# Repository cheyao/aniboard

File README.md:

# Aniboard - Anime themed keyboard

*Insert Final Product Picture*

Made by cyao: `@Cyao` on slack, github.com/cheyao

Features:
- 88x keys!
- Morally correct Alt, Command, Control layout
- 0.91" OLED for your favourite pictures
- 88x Neopixels capable of eating 5.28A! Portable hand warmer :3
- Optional triple USB power input to feed all the hungry neopixels.
- Cute anime silkscreens! (Open PCB in KiCAD and zoom out to find a easter egg :3)
- Adaptive power MUXing and overcurrent fail safes
- Multiple fail safes, optional solder bridge configs
- Super compact design
- Self define tilt (Go edit in `CAD/constants.scad` and regenerate)
- Employes metal electrode leadless face technology to ensure high-reliability and precision with predictable characteristics
- High accuracy, long-term stability, moisture resistance, high-temperature resistance
- Made with precise Hot Air solder reflow technology
- KMK firmware, live edit your keymaps

## PCB 

The PCB's size is 355x120mm

| Schematic |
| - |
|  |

| Two sides |
| - |
|  |

| Front |
| - |
|  |

| Back |
| - |
|  |

3D render pictures:

## Case

The case v1 is fully parametric and made with OpenSCAD, allowed me to make a online case generator. Link after the YSWS ends.

V2 is made with freecad, and is of top mount style.

I chose to not add any engraving since it will look bad. I would want to print my case In school with ams and custom colored fillament when I buy some new fillament. (I need hq to print my case in white for the moment)

## BOM

These were old prices for aliexpress, see bottom for lcsc prices (better)

| Name                             | Qty | Price (EUR) |
| -------------------------------- | --- | ----------- |
| 0.91" OLED SSD1306               | 1   | |
| 0.1uf 0805 capacitors            | 90  | |
| 4.7uf 0805 capacitors            | 3   | |
| 1uf   0805 capacitor             | 3   | |
| MiniMELF diodes                  | 88  | |
| 0603 GLED Vf2.1 30mA             | 7   | |
| USB-C Receptacles                | 2   | |
| SK6812MINI-E                     | 88  | |
| 470Ω 0805 resistor               | 5   | |
| 4.7kΩ 0805 resistor              | 5   | |
| 5.1kΩ 0805 resistor              | 4   | |
| 10kΩ 0805 resistor               | 2   | |
| 1kΩ 0805 resistor                | 2   | |
| 200Ω 0805 resistor               | 3   | |
| TPS2116DRL                       | 2   | |
| SN74LVC1T45DBVR                  | 1   | |
| CH224K                           | 2   | |
| ESP12-E                          | 1   | |
| Orph/Raspberry Pi Pico           | 1   | High Seas   |
| Case (Preferably pink, else white "./production/case.3mf") | 1 | Me |
| Acrylic ("./production/acrylic.dxf") | 1 | Hack Club |
| M2 Heatset Inserts 4OD 4mm       | 28  | 1.74        |
| M2 Torx Thin Head Bolts 5mm 14mm | 16  | 2.08        |
| M2 Torx Thin Head Bolts 5mm 5mm  | 12  | 1.62        |
| JWK Cupid Switch                 | 88  | 36.60/w ship|
| 2u MX stabilizor                 | 5   | 27.99 (20$ new member) |
| 6.25u MX stabilizer              | 1   | ^           |

Old:

| Total Price | PCB      | Switches | Fasteners | Keycaps  | Stabilizers | Other     |
| ----------- | -------- | -------- | --------- | -------- | ----------- | --------- |
| 120.63/ws   | 37.00/ws | 38.81/ws | 5.44/ns   | 21.79/ws | 19.59/ns    | ~24.03/ws |

2$ More in PCB for lead free HASL!

Please add this grant to my High Seas Digikey grant! <3

~The stabs are 22.38 USD so going to transfer 5$ to HQ.~ Done, https://hcb.hackclub.com/hackpad/donations - Chengyin Yao aka Cyao

~Uhh I think the TX are still over budget? Gonna figure something out.~ Found in budget TX! Gonna abuse new member discount lol.

The LCSC cart might seem to have excess of some components, it's either: minimal quanitity, or at the end I could spend 2.7$ more to save 6$ so why not

Cupid: https://keygem.com/products/cupid-switch-group-buy-10pcs?variant=44806087770380

## Notes:

This got me 60h on cafe :sob:

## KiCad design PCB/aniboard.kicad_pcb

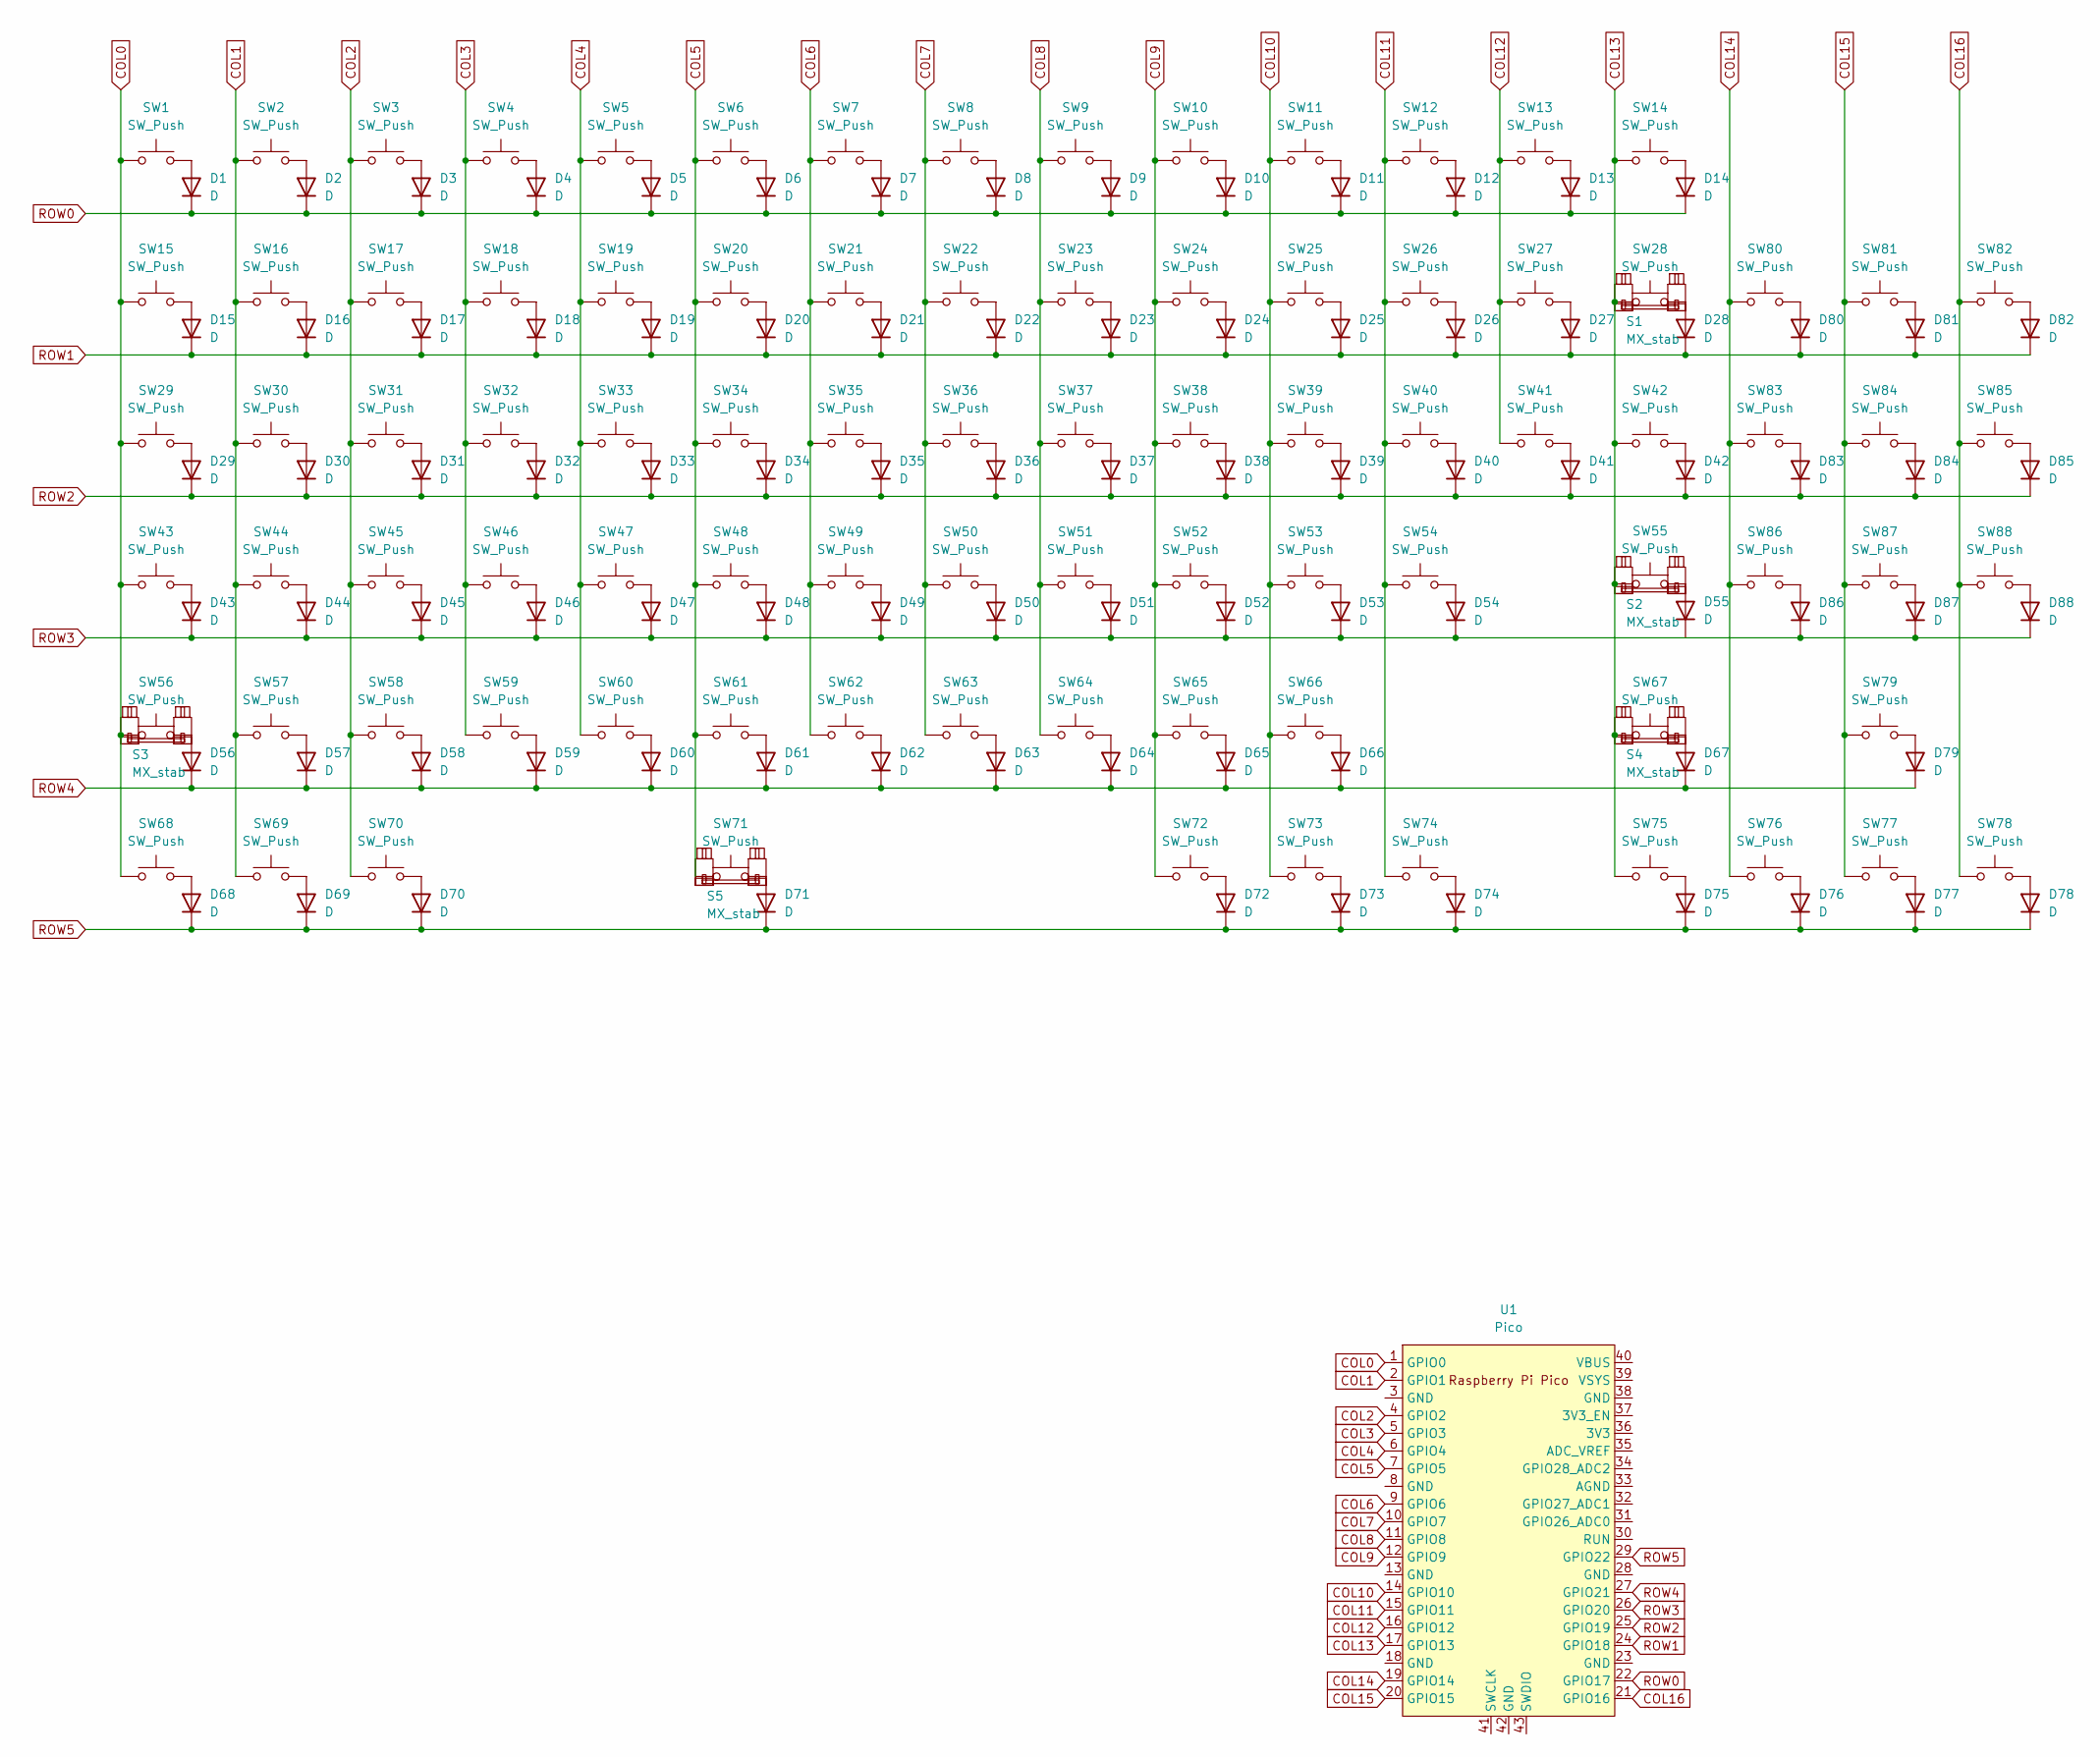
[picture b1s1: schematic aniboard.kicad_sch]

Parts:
D1, D2, D3, D4, D5, D6, D7, D8, D9, D10, D11, D12, D13, D14, D15, D16, D17, D18, D19, D20, D21, D22, D23, D24, D25, D26, D27, D28, D29, D30, D31, D32, D33, D34, D35, D36, D37, D38, D39, D40, D41, D42, D43, D44, D45, D46, D47, D48, D49, D50, D51, D52, D53, D54, D55, D56, D57, D58, D59, D60, D61, D62, D63, D64, D65, D66, D67, D68, D69, D70, D71, D72, D73, D74, D75, D76, D77, D78, D79, D80, D81, D82, D83, D84, D85, D86, D87, D88: D; D_DO-35_SOD27_P7.62mm_Horizontal
S1: MX_stab; STAB_MX_2u
S2, S3: MX_stab; STAB_MX_2.25u
S4: MX_stab; STAB_MX_2.75u
S5: MX_stab; STAB_MX_6.25u
SW1, SW14, SW29, SW42: SW_Push; SW_MX_1.5u
SW2, SW3, SW4, SW5, SW6, SW7, SW8, SW9, SW10, SW11, SW12, SW13, SW15, SW16, SW17, SW18, SW19, SW20, SW21, SW22, SW23, SW24, SW25, SW26, SW27, SW28, SW30, SW31, SW32, SW33, SW34, SW35, SW36, SW37, SW38, SW39, SW40, SW41, SW44, SW45, SW46, SW47, SW48, SW49, SW50, SW51, SW52, SW53, SW54, SW55, SW56, SW57, SW58, SW59, SW60, SW61, SW62, SW63, SW64, SW65, SW66, SW67, SW71, SW76, SW77, SW78, SW79, SW80, SW81, SW82, SW83, SW84, SW85, SW86, SW87, SW88: SW_Push; SW_MX_1u
SW43: SW_Push; SW_MX_1.75u
SW68, SW69, SW70, SW72, SW73, SW74, SW75: SW_Push; SW_MX_1.25u
U1: Pico; RPi_Pico_SMD_TH

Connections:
COL0: SW1.1, SW15.1, SW29.1, SW43.1, SW56.1, SW68.1, U1.1 (GPIO0)
COL1: SW2.1, SW16.1, SW30.1, SW44.1, SW57.1, SW69.1, U1.2 (GPIO1)
COL2: SW3.1, SW17.1, SW31.1, SW45.1, SW58.1, SW70.1, U1.4 (GPIO2)
COL3: SW4.1, SW18.1, SW32.1, SW46.1, SW59.1, U1.5 (GPIO3)
COL4: SW5.1, SW19.1, SW33.1, SW47.1, SW60.1, U1.6 (GPIO4)
COL5: SW6.1, SW20.1, SW34.1, SW48.1, SW61.1, SW71.1, U1.7 (GPIO5)
COL6: SW7.1, SW21.1, SW35.1, SW49.1, SW62.1, U1.9 (GPIO6)
COL7: SW8.1, SW22.1, SW36.1, SW50.1, SW63.1, U1.10 (GPIO7)
COL8: SW9.1, SW23.1, SW37.1, SW51.1, SW64.1, U1.11 (GPIO8)
COL9: SW10.1, SW24.1, SW38.1, SW52.1, SW65.1, SW72.1, U1.12 (GPIO9)
COL10: SW11.1, SW25.1, SW39.1, SW53.1, SW66.1, SW73.1, U1.14 (GPIO10)
COL11: SW12.1, SW26.1, SW40.1, SW54.1, SW74.1, U1.15 (GPIO11)
COL12: SW13.1, SW27.1, SW41.1, U1.16 (GPIO12)
COL13: SW14.1, SW28.1, SW42.1, SW55.1, SW67.1, SW75.1, U1.17 (GPIO13)
COL14: SW76.1, SW80.1, SW83.1, SW86.1, U1.19 (GPIO14)
COL15: SW77.1, SW79.1, SW81.1, SW84.1, SW87.1, U1.20 (GPIO15)
COL16: SW78.1, SW82.1, SW85.1, SW88.1, U1.21 (GPIO16)
unnamed: D1.2 (A), SW1.2
unnamed: D2.2 (A), SW2.2
unnamed: D3.2 (A), SW3.2
unnamed: D4.2 (A), SW4.2
unnamed: D5.2 (A), SW5.2
unnamed: D6.2 (A), SW6.2
unnamed: D7.2 (A), SW7.2
unnamed: D8.2 (A), SW8.2
unnamed: D9.2 (A), SW9.2
unnamed: D10.2 (A), SW10.2
unnamed: D11.2 (A), SW11.2
unnamed: D12.2 (A), SW12.2
unnamed: D13.2 (A), SW13.2
unnamed: D14.2 (A), SW14.2
unnamed: D15.2 (A), SW15.2
unnamed: D16.2 (A), SW16.2
unnamed: D17.2 (A), SW17.2
unnamed: D18.2 (A), SW18.2
unnamed: D19.2 (A), SW19.2
unnamed: D20.2 (A), SW20.2
unnamed: D21.2 (A), SW21.2
unnamed: D22.2 (A), SW22.2
unnamed: D23.2 (A), SW23.2
unnamed: D24.2 (A), SW24.2
unnamed: D25.2 (A), SW25.2
unnamed: D26.2 (A), SW26.2
unnamed: D27.2 (A), SW27.2
unnamed: D28.2 (A), SW28.2
unnamed: D29.2 (A), SW29.2
unnamed: D30.2 (A), SW30.2
unnamed: D31.2 (A), SW31.2
unnamed: D32.2 (A), SW32.2
unnamed: D33.2 (A), SW33.2
unnamed: D34.2 (A), SW34.2
unnamed: D35.2 (A), SW35.2
unnamed: D36.2 (A), SW36.2
unnamed: D37.2 (A), SW37.2
unnamed: D38.2 (A), SW38.2
unnamed: D39.2 (A), SW39.2
unnamed: D40.2 (A), SW40.2
unnamed: D41.2 (A), SW41.2
unnamed: D42.2 (A), SW42.2
unnamed: D43.2 (A), SW43.2
unnamed: D44.2 (A), SW44.2
unnamed: D45.2 (A), SW45.2
unnamed: D46.2 (A), SW46.2
unnamed: D47.2 (A), SW47.2
unnamed: D48.2 (A), SW48.2
unnamed: D49.2 (A), SW49.2
unnamed: D50.2 (A), SW50.2
unnamed: D51.2 (A), SW51.2
unnamed: D52.2 (A), SW52.2
unnamed: D53.2 (A), SW53.2
unnamed: D54.2 (A), SW54.2
unnamed: D55.2 (A), SW55.2
unnamed: D56.2 (A), SW56.2
unnamed: D57.2 (A), SW57.2
unnamed: D58.2 (A), SW58.2
unnamed: D59.2 (A), SW59.2
unnamed: D60.2 (A), SW60.2
unnamed: D61.2 (A), SW61.2
unnamed: D62.2 (A), SW62.2
unnamed: D63.2 (A), SW63.2
unnamed: D64.2 (A), SW64.2
unnamed: D65.2 (A), SW65.2
unnamed: D66.2 (A), SW66.2
unnamed: D67.2 (A), SW67.2
unnamed: D68.2 (A), SW68.2
unnamed: D69.2 (A), SW69.2
unnamed: D70.2 (A), SW70.2
unnamed: D71.2 (A), SW71.2
unnamed: D72.2 (A), SW72.2
unnamed: D73.2 (A), SW73.2
unnamed: D74.2 (A), SW74.2
unnamed: D75.2 (A), SW75.2
unnamed: D76.2 (A), SW76.2
unnamed: D77.2 (A), SW77.2
unnamed: D78.2 (A), SW78.2
unnamed: D79.2 (A), SW79.2
unnamed: D80.2 (A), SW80.2
unnamed: D81.2 (A), SW81.2
unnamed: D82.2 (A), SW82.2
unnamed: D83.2 (A), SW83.2
unnamed: D84.2 (A), SW84.2
unnamed: D85.2 (A), SW85.2
unnamed: D86.2 (A), SW86.2
unnamed: D87.2 (A), SW87.2
unnamed: D88.2 (A), SW88.2
ROW0: D1.1 (K), D2.1 (K), D3.1 (K), D4.1 (K), D5.1 (K), D6.1 (K), D7.1 (K), D8.1 (K), D9.1 (K), D10.1 (K), D11.1 (K), D12.1 (K), D13.1 (K), D14.1 (K), U1.22 (GPIO17)
ROW1: D15.1 (K), D16.1 (K), D17.1 (K), D18.1 (K), D19.1 (K), D20.1 (K), D21.1 (K), D22.1 (K), D23.1 (K), D24.1 (K), D25.1 (K), D26.1 (K), D27.1 (K), D28.1 (K), D80.1 (K), D81.1 (K), D82.1 (K), U1.24 (GPIO18)
ROW2: D29.1 (K), D30.1 (K), D31.1 (K), D32.1 (K), D33.1 (K), D34.1 (K), D35.1 (K), D36.1 (K), D37.1 (K), D38.1 (K), D39.1 (K), D40.1 (K), D41.1 (K), D42.1 (K), D83.1 (K), D84.1 (K), D85.1 (K), U1.25 (GPIO19)
ROW3: D43.1 (K), D44.1 (K), D45.1 (K), D46.1 (K), D47.1 (K), D48.1 (K), D49.1 (K), D50.1 (K), D51.1 (K), D52.1 (K), D53.1 (K), D54.1 (K), D86.1 (K), D87.1 (K), D88.1 (K), U1.26 (GPIO20)
ROW4: D56.1 (K), D57.1 (K), D58.1 (K), D59.1 (K), D60.1 (K), D61.1 (K), D62.1 (K), D63.1 (K), D64.1 (K), D65.1 (K), D66.1 (K), D67.1 (K), D79.1 (K), U1.27 (GPIO21)
ROW5: D68.1 (K), D69.1 (K), D70.1 (K), D71.1 (K), D72.1 (K), D73.1 (K), D74.1 (K), D75.1 (K), D76.1 (K), D77.1 (K), D78.1 (K), U1.29 (GPIO22)

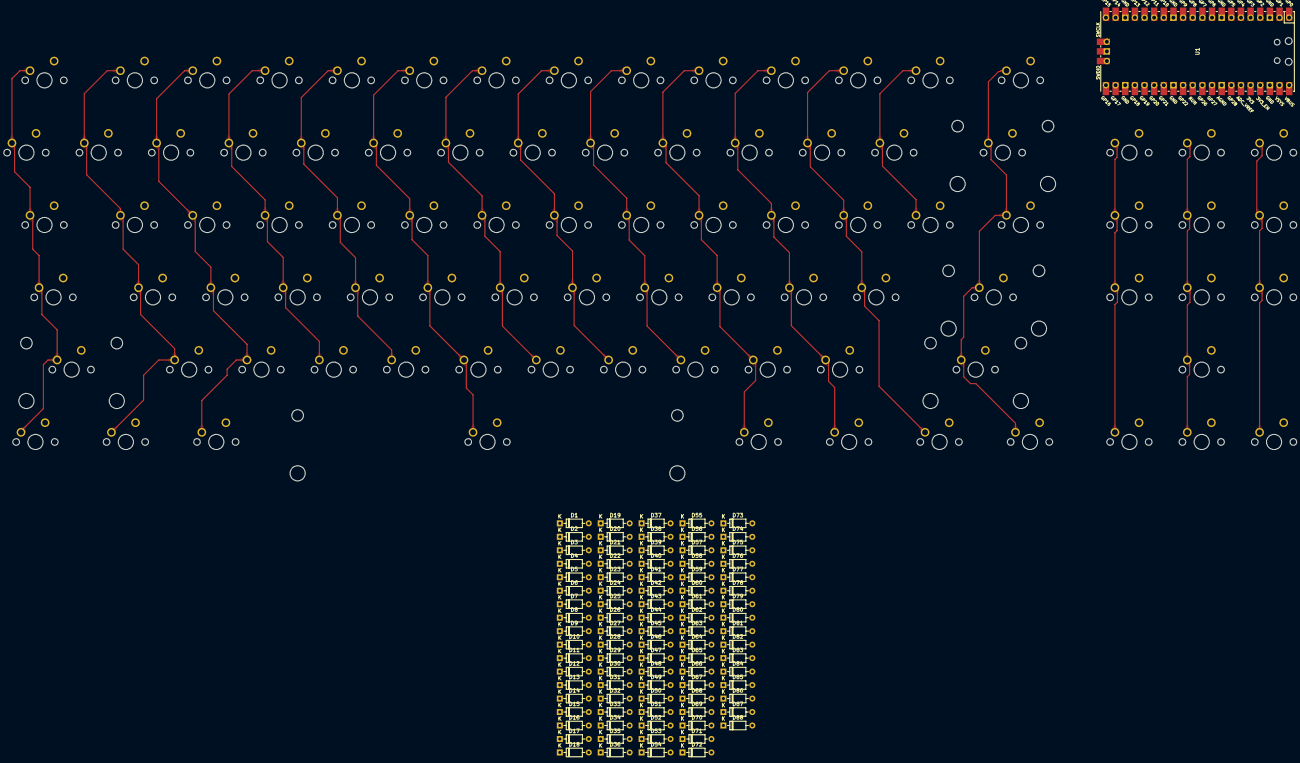
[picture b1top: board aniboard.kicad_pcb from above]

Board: 2 copper layers, 182 parts (0 on the bottom side), 111 nets.

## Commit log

2025-02-02 Start of aniboard
2025-02-02 First three rows
2025-02-02 Keyboard layout
2025-02-02 Continue routing PCB
2025-02-05 Finish column routing
2025-02-06 More keyboard
2025-02-06 Added neopixels
2025-02-06 Placed diodes
2025-02-06 Partial routing
2025-02-11 Save
2025-02-12 Half done with routing
2025-02-12 Finish routing
2025-02-13 V1.2
2025-02-14 Finish PCB and top plate
2025-02-14 Finish Plate
2025-02-14 Finish case
2025-02-15 Fix coplanar surfaces
2025-02-15 Assembly hotfix
2025-02-15 Hotfix
2025-02-15 Remove stuff
2025-02-15 Fix render bug
2025-02-15 Render
2025-02-15 Start of firmware
2025-02-16 Finish firmware
2025-02-16 Update pcb
2025-02-16 Reexport using freecad
2025-02-16 Reroute and silkscreen
2025-02-17 Last pass
2025-02-20 Dual USB powah
2025-02-22 Change switches
2025-02-22 Improve picture layout
2025-02-22 Better images
2025-02-22 Fix tolarences
2025-02-23 Add LCSC price
2025-02-24 Fix mounting hole error
2025-02-26 Update BOM
2025-02-26 Add mail fee
2025-03-07 Redesign v2!
2025-03-07 Pics
2025-03-08 Add license
2025-03-09 Thing
2025-03-09 Fix case
2025-03-11 RX TX Breakout
2025-03-12 Modular case
2025-03-12 Better pics
2025-03-16 Lead free HASL
2025-10-06 Add STEP
2025-10-25 Finally ordered
2025-10-31 Add ibom
